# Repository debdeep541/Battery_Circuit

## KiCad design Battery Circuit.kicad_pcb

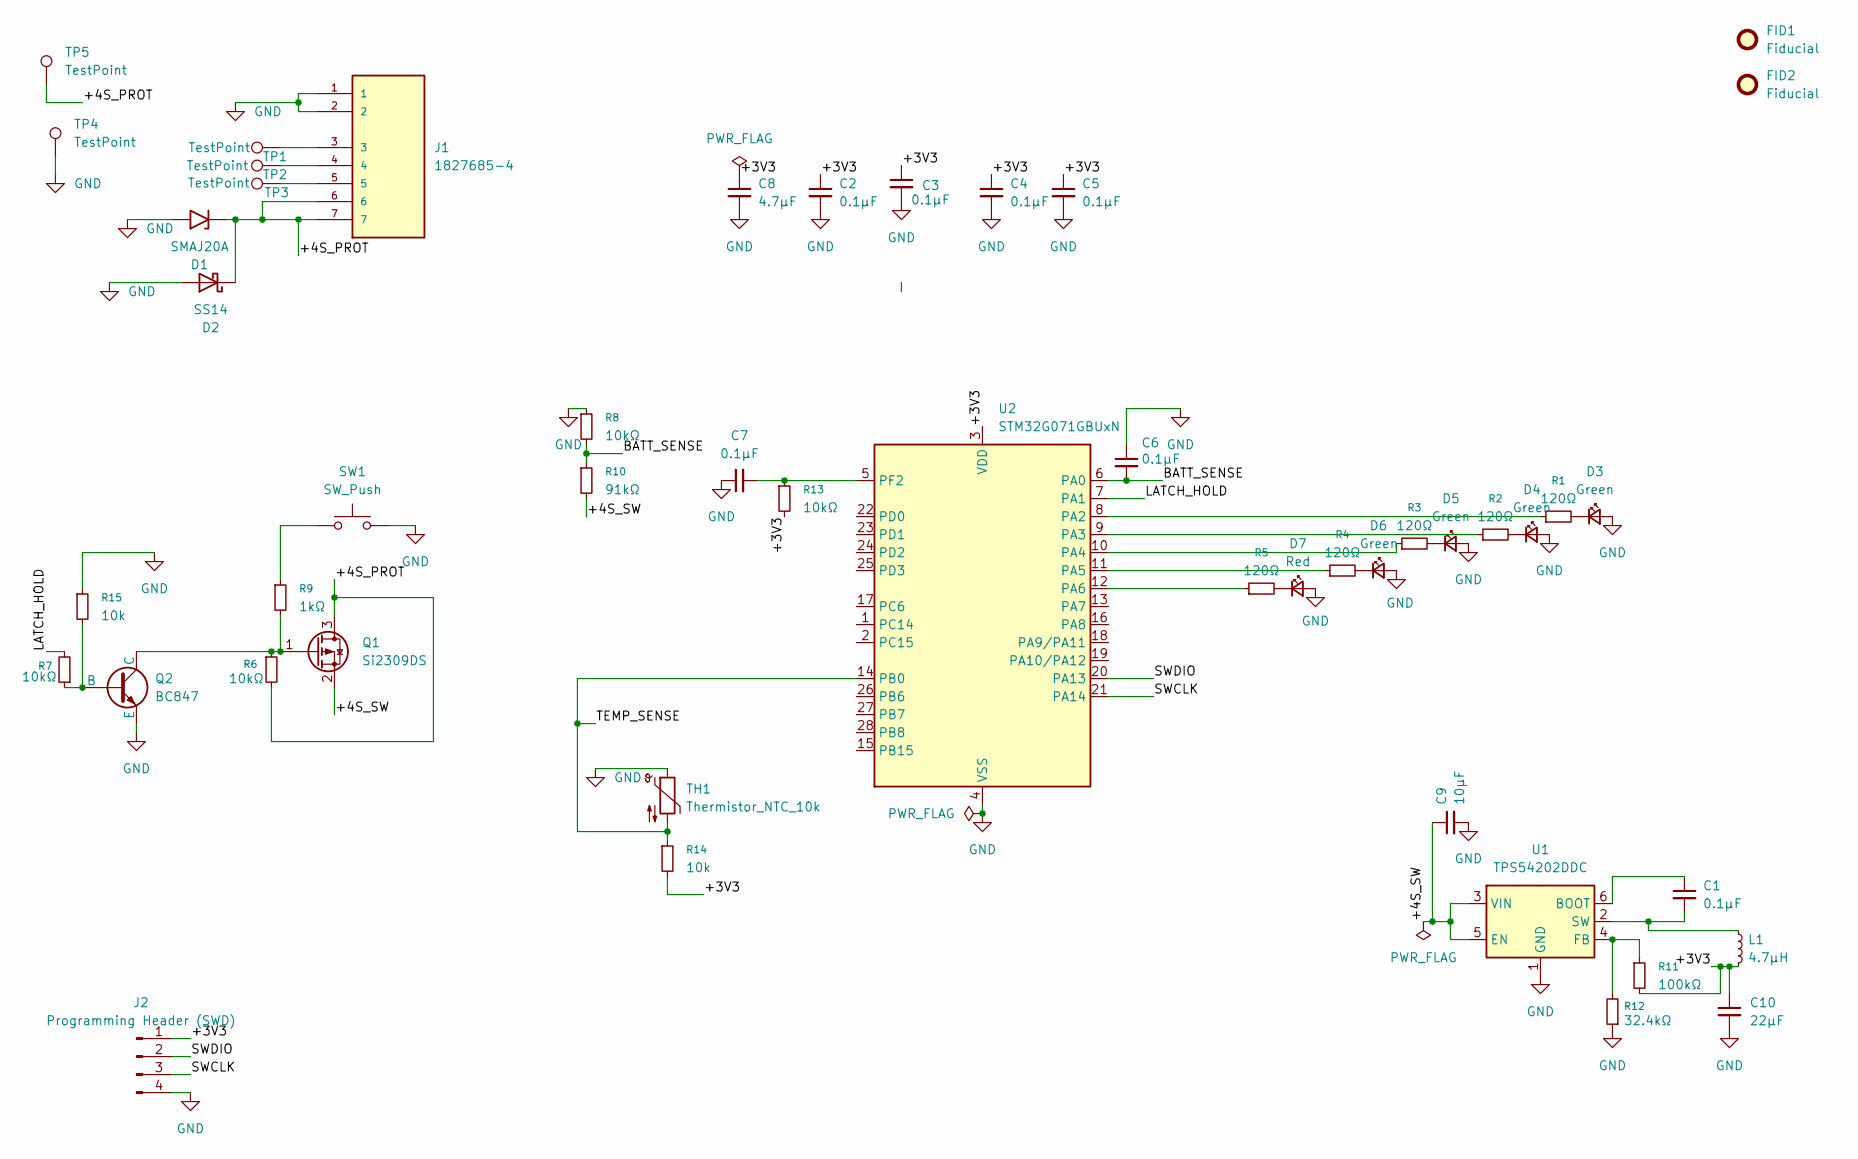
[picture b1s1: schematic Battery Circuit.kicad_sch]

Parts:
C1, C2, C3, C4, C5, C6, C7: 0.1µF; C_0402_1005Metric
C8: 4.7µF; C_0603_1608Metric
C9: 10µF; C_0805_2012Metric
C10: 22µF; C_0805_2012Metric
D1: SMAJ20A; D_SMA
D2: SS14; D_SMA
D3, D4, D5, D6: Green; LED_0603_1608Metric
D7: Red; LED_0603_1608Metric
FID1, FID2: Fiducial; Fiducial_1mm_Mask2mm
J1: 1827685-4; TE_1827685-4; DigiKey_Part_Number A139165-ND
J2: Programming Header (SWD); PinHeader_1x04_P2.54mm_Vertical
L1: 4.7µH; L_Bourns-SRN4018
Q1: Si2309DS; SOT-23
Q2: BC847; SOT-23
R1, R2, R3, R4, R5: 120Ω; R_0402_1005Metric
R6, R7, R8, R13: 10kΩ; R_0402_1005Metric
R9: 1kΩ; R_0402_1005Metric
R10: 91kΩ; R_0402_1005Metric
R11: 100kΩ; R_0402_1005Metric
R12: 32.4kΩ; R_0402_1005Metric
R14, R15: 10k; R_0402_1005Metric
SW1: SW_Push; SW_SPST_B3U-1000P
TH1: Thermistor_NTC_10k; R_0402_1005Metric
TP1, TP2, TP3, TP4, TP5: TestPoint; TestPoint_Pad_3.0x3.0mm
U1: TPS54202DDC; SOT-23-6
U2: STM32G071GBUxN; QFN-28_4x4mm_P0.5mm

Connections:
/+3V3: C2.1, C3.1, C4.1, C5.1, C8.1, C10.1, J2.1, L1.2, R11.2, R13.2, R14.2, U2.3 (VDD)
/+4S_PROT: D1.1 (A1), D2.1 (K), J1.6, J1.7, Q1.3 (D), R6.2, TP5.1 (1_1)
/+4S_SW: C9.1, Q1.2 (S), R10.2, U1.3 (VIN), U1.5 (EN)
/BATT_SENSE: C6.2, R8.2, R10.1, U2.6 (PA0)
/LATCH_HOLD: R7.2, U2.7 (PA1)
/SWCLK: J2.3, U2.21 (PA14)
/SWDIO: J2.2, U2.20 (PA13)
/TEMP_SENSE: R14.1, TH1.2, U2.14 (PB0)
GND: C2.2, C3.2, C4.2, C5.2, C6.1, C7.1, C8.2, C9.2, C10.2, D1.2 (A2), D2.2 (A), D3.2 (A), D4.2 (A), D5.2 (A), D6.2 (A), D7.2 (A), J1.1, J1.2, J2.4, Q2.3 (E), R8.1, R12.1, R15.1, SW1.2, TH1.1, TP4.1 (1_1), U1.1 (GND), U2.4 (VSS)
unnamed: D3.1 (K), R1.2
unnamed: D4.1 (K), R2.2
unnamed: D5.1 (K), R3.2
unnamed: D6.1 (K), R4.2
unnamed: D7.1 (K), R5.2
unnamed: J1.3, TP1.1 (1_1)
unnamed: J1.4, TP2.1 (1_1)
unnamed: J1.5, TP3.1 (1_1)
unnamed: Q1.1 (G), Q2.1 (C), R6.1, R9.2
unnamed: Q2.2 (B), R7.1, R15.2
unnamed: R9.1, SW1.1
unnamed: C1.1, U1.6 (BOOT)
unnamed: R11.1, R12.2, U1.4 (FB)
unnamed: C1.2, L1.1, U1.2 (SW)
unnamed: R1.1, U2.8 (PA2)
unnamed: R2.1, U2.9 (PA3)
unnamed: R3.1, U2.10 (PA4)
unnamed: R4.1, U2.11 (PA5)
unnamed: R5.1, U2.12 (PA6)
unnamed: C7.2, R13.1, U2.5 (PF2)

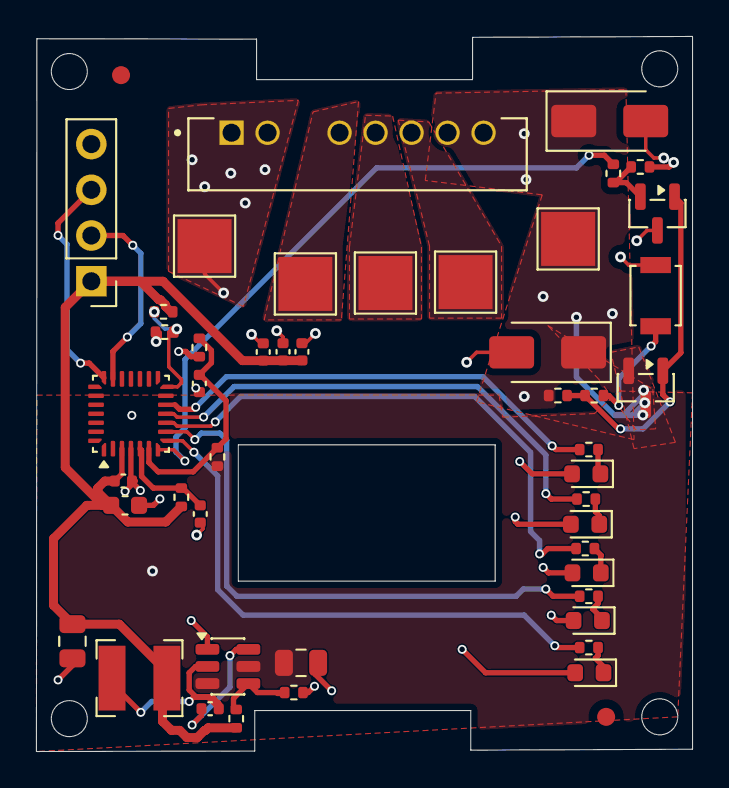
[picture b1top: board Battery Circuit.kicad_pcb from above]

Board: 4 copper layers, 36.4 x 39.7 mm, 48 parts (0 on the bottom side), 29 nets.

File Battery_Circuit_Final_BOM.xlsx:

Item | Designator(s) | Qty | Value / Part | Footprint | Component Type | Functional Description / Working
1 | C1, C2, C3, C4, C5, C6, C7 | 7 | 0.1µF | C_0402_1005Metric | Capacitor | Decoupling capacitors to filter high-frequency noise near the MCU and IC power 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
2 | C8 | 1 | 4.7µF | C_0603_1608Metric | Capacitor | Input/Output filtering for the TPS54202DDC buck converter.
3 | C9 | 1 | 10µF | C_0805_2012Metric | Capacitor | Smoothing capacitor for the regulated 3.3V power rail.
4 | C10 | 1 | 22µF | C_0805_2012Metric | Capacitor | Bulk output capacitance for the buck converter to maintain stable voltage under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
5 | D1 | 1 | SMAJ20A | D_SMA | TVS Diode | 20V Transient Voltage Suppressor. Clamps dangerous voltage spikes to protect th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
6 | D2 | 1 | SS14 | D_SMA | Schottky Diode | Provides reverse polarity protection and handles inductive flyback currents fro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
7 | D3, D4, D5, D6 | 4 | Green LED | LED_0603_1608Metric | LED | Visual battery capacity indicators mapped to voltage thresholds (25%, 50%, 75%,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
8 | D7 | 1 | Red LED | LED_0603_1608Metric | LED | Emergency fault indicator (Triggers on Overvoltage >17.5V, Undervoltage <15V, o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
9 | FID1, FID2 | 2 | Fiducial | Fiducial_1mm_Mask2mm | Optical Marker | Asymmetrical corner reference markers for the NeoDen YY1 pick-and-place machine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
10 | J1 | 1 | 1827685-4 | TE_1827685-4 | Connector | Main high-current battery/power terminal connector.
11 | J2 | 1 | SWD Header | PinHeader_1x04_P2.54mm_Vertical | Connector | 4-pin SWD interface used to program and debug the STM32 via ST-Link.
12 | L1 | 1 | 4.7µH | L_Bourns-SRN4018 | Inductor | Main energy storage inductor for the TPS54202 switching buck converter.
13 | Q1 | 1 | Si2309DS | SOT-23 | MOSFET (P-Channel) | Main power switch. Physically cuts off power to the load during an emergency ha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
14 | Q2 | 1 | BC847 | SOT-23 | BJT (NPN) | Logic-level gate driver controlled by the MCU to pull down and turn Q1 (MOSFET)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
15 | R1, R2, R3, R4, R5 | 5 | 120Ω | R_0402_1005Metric | Resistor | Current limiting resistors configured for higher LED brightness (~10mA draw).
16 | R6, R7, R8, R13 | 4 | 10kΩ | R_0402_1005Metric | Resistor | Pull-up/pull-down resistors for stabilizing logic lines and preventing floating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
17 | R9 | 1 | 1kΩ | R_0402_1005Metric | Resistor | Base current limiting resistor for the BC847 NPN transistor.
18 | R10 | 1 | 91kΩ | R_0402_1005Metric | Resistor | High-side resistor for the main battery voltage divider (scaling 18V down to 3.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
19 | R11 | 1 | 100kΩ | R_0402_1005Metric | Resistor | Additional voltage scaling or logic line pull-down resistor.
20 | R12 | 1 | 32.4kΩ | R_0402_1005Metric | Resistor | Precision resistor setting the feedback voltage loop for the TPS54202DDC buck c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
21 | R14 | 1 | 10kΩ | R_0402_1005Metric | Resistor | Top/Bottom leg of the thermistor voltage divider.
22 | SW1 | 1 | SW_Push | SW_SPST_B3U-1000P | Switch | Tactile push button for user interaction (e.g., wake device or check battery le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
23 | TH1 | 1 | 10k NTC | R_0402_1005Metric | Thermistor | Thermal sensor. Resistance drops as heat rises; MCU triggers emergency shutdown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
24 | TP1, TP2, TP3, TP4, TP5 | 5 | TestPoint | TestPoint_Pad_3.0x3.0mm | Test Point | Exposed copper pads for multimeter probing and automated QA testing during asse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
25 | U1 | 1 | TPS54202DDC | SOT-23-6 | Buck Converter | Steps down the high 15.4V-18V battery voltage to a safe, stable 3.3V to power t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
26 | U2 | 1 | STM32G071GBUxN | Package_DFN_QFN:QFN-28_4x4mm_P0.5mm | Microcontroller | The 28-pin MCU brain. Runs the firmware, polls ADC sensors, and commands Q1 cut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

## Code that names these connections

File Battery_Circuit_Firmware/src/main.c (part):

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 * Rule 7: Hardware stop saves lives. Drops latch pin to physically cut power.
 */
void executeEmergencyStop(void) {
    // Cut main power via MOSFET (PF2) and drop LATCH_HOLD (PA1)
    HAL_GPIO_WritePin(GPIOF, GPIO_PIN_2, GPIO_PIN_RESET); 
    HAL_GPIO_WritePin(GPIOA, GPIO_PIN_1, GPIO_PIN_RESET); 
    
    // Turn ON Red Fault LED (PA6)
    HAL_GPIO_WritePin(GPIOA, GPIO_PIN_6, GPIO_PIN_SET);
    
    // Turn OFF all Green LEDs (PA2-PA5) to signal shutdown
    HAL_GPIO_WritePin(GPIOA, GPIO_PIN_2|GPIO_PIN_3|GPIO_PIN_4|GPIO_PIN_5, GPIO_PIN_RESET);
}

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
